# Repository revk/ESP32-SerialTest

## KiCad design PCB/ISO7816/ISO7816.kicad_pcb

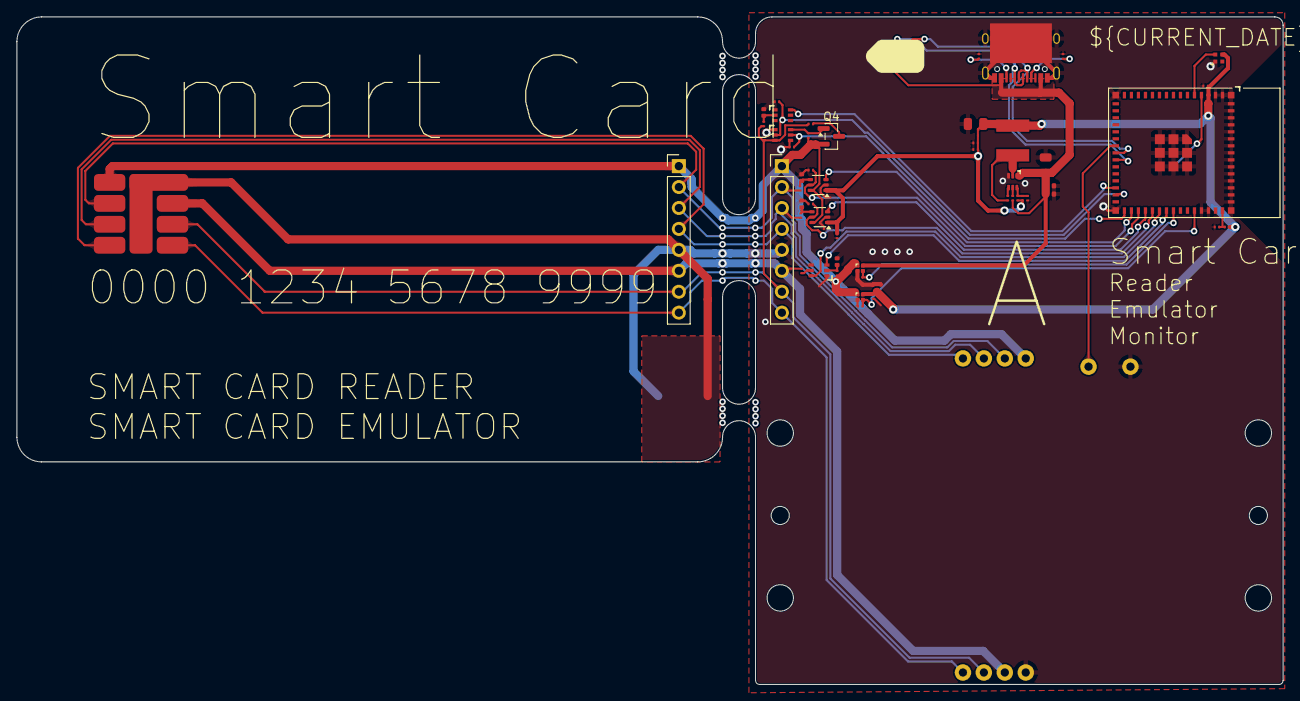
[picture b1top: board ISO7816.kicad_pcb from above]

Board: 2 copper layers, 153.6 x 81.0 mm, 54 parts (1 on the bottom side), 40 nets.

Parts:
C6: 1uF; C_0201
C15: 22uF 25V; C_0805
C16, C17: 100nF 25V; C_0402
C18, C21, C22, C23, C24, C25: 100nF; C_0201
C19: 18pF; C_0201
C20: 47uF 6V; C_0805
D1: XL-1010RGBC-WS2812B; SMD1010
D2, D3, D5, D6: DFN1006-2L
J1: Conn_01x02; AA-Pad
J2: ISO7816
J3, J4: Conn_01x08; PinHeader_1x08_P2.54mm_Vertical
J5: 7434L0825S01LF
J6: USB-C-Socket-H
J7: TC2030-USB-NL-DS; Tag-Connect_TC2030-IDC-NL_2x03_P1.27mm_Vertical
L2: 4.7uH; L_5x5
Q1, Q2, Q3: BSS138PS; SOT-363_SC-70-6
Q4: BSS84; SOT-23
R1: 20k; R_0201
R2, R3, R4, R12, R13, R17, R18, R19: 10k; R_0201
R5, R6, R8, R9, R20: 10R; R_0201
R10, R11: 5K1; R_0201
R14, R15: 150k 1%; R_0201
R16: 33k 1%; R_0201
U1: ESP32-S3-MINI-1-N4R2; ESP32-S3-MINI-1
U2, U6: SN74LVC1T45DCK; SOT-363_SC-70-6
U3: TPS562246; SOT-563
U4, U5: TPS22916CNYFPR; WCSP-4-0.78x0.78

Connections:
+3.3V: C19.2, C20.1, C21.2, C22.2, C23.2, C24.2, C25.2, D1.3 (-), L2.2, R2.1, R15.1, U1.3 (3V3), U2.1 (VCCA), U5.A2 (VIN), U6.1 (VCCA)
BST: C18.1, U3.4 (VBST)
C_3V3: R13.1, U1.41 (GPIO45), U5.B2 (ON)
C_4: J2.4 (C4), J3.4, J4.4, J5.4 (C4)
C_5V: R12.1, U1.38 (GPIO42), U4.B2 (ON)
C_8: J2.8 (C8), J3.8, J4.8, J5.8 (C8)
C_CLK: J2.3 (CLK), J3.3, J4.3, J5.3 (CLK), R8.2
C_CLK_E: R18.2, U1.35 (GPIO39), U6.5 (DIR)
C_CLK_IO: U1.34 (GPIO38), U6.3 (A)
C_INSERT: J5.9 (I1), U1.22 (GPIO18)
C_I/O: J2.7 (I/O), J3.7, J4.7, J5.7 (I/O), Q3.3 (SP), R1.2, R9.2
C_I/O_E: Q3.2 (GN), R4.2, U1.29 (GPIO34)
C_I/O_I: Q2.6 (DN), U1.28 (GPIO33)
C_I/O_O: Q3.5 (GP), R17.1, U1.31 (GPIO35)
C_RST: J2.2 (RST), J3.2, J4.2, J5.2 (RST), R20.2
C_RST_E: R19.2, U1.33 (GPIO37), U2.5 (DIR)
C_RST_IO: U1.32 (GPIO36), U2.3 (A)
C_VCC: J2.1 (VCC), J3.1, J4.1, J5.1 (VCC), Q4.2 (S), R3.2, R5.2, U2.6 (VCCB), U4.A1 (VOUT), U5.A1 (VOUT), U6.6 (VCCB)
C_VCC_I: Q1.6 (DN), U1.36 (GPIO40)
C_VPP: J2.6 (VPP), J3.6, J4.6, J5.6 (VPP), R6.2
C_VPP_I: Q1.3 (SP), U1.37 (GPIO41)
D+: J6.A6 (D+), J6.B6 (D+), J7.4 (D+), U1.24 (GPIO20)
D-: J6.A7 (D-), J6.B7 (D-), J7.2 (NC), J7.3 (D-), J7.6 (NC), U1.23 (GPIO19)
EN: R14.1, U3.5 (EN)
FB: C19.1, R15.2, R16.1, U3.6 (VFB)
GND: C6.2, C15.2, C16.2, C17.2, C20.2, C21.1, C22.1, C23.1, C24.1, C25.1, D1.2 (+), D2.1, D3.1, D5.1, D6.1, J1.1, J2.5 (GND), J3.5, J4.5, J5.5 (GND), J5.10 (I2), J6.A1 (GND), J6.A12 (GND), J6.B1 (GND), J6.B12 (GND), J6.S1 (SHIELD), J7.5 (GND), Q1.1 (SN), Q1.4 (DP), Q2.1 (SN), Q3.1 (SN), Q3.4 (DP), R4.1, R10.2, R11.1, R12.2, R13.2, R16.2, R17.2, R18.1, R19.1, U1.1 (GND), U1.2 (GND), U1.42 (GND), U1.43 (GND), U1.46 (GND), U1.47 (GND), U1.48 (GND), U1.49 (GND), U1.50 (GND), U1.51 (GND), U1.52 (GND), U1.53 (GND), U1.54 (GND), U1.55 (GND), U1.56 (GND), U1.57 (GND), U1.58 (GND), U1.59 (GND), U1.60 (GND), U1.61 (GND), U1.62 (GND), U1.63 (GND), U1.64 (GND), U1.65 (GND), U2.2 (GND), U3.3 (GND), U4.B1 (GND), U5.B1 (GND), U6.2 (GND)
LED: D1.4 (I), U1.5 (GPIO1)
unnamed: J1.2, U1.4 (GPIO0)
unnamed: J6.A5 (CC1), R10.1
unnamed: J6.B5 (CC2), R11.2
unnamed: D2.2, Q1.2 (GN), R5.1
unnamed: Q1.5 (GP), R6.1
unnamed: D6.2, Q2.2 (GN), R9.1
unnamed: Q3.6 (DN), Q4.1 (G), R3.1
unnamed: Q4.3 (D), R1.1
unnamed: C6.1, R2.2, U1.45 (EN)
unnamed: D3.2, R20.1, U2.4 (B)
unnamed: D5.2, R8.1, U6.4 (B)
SW: C18.2, L2.1, U3.2 (SW)
VBUS: C15.1, C16.1, C17.1, J6.A4 (VBUS), J6.A9 (VBUS), J6.B4 (VBUS), J6.B9 (VBUS), J7.1 (VBUS), R14.2, U3.1 (VIN), U4.A2 (VIN)

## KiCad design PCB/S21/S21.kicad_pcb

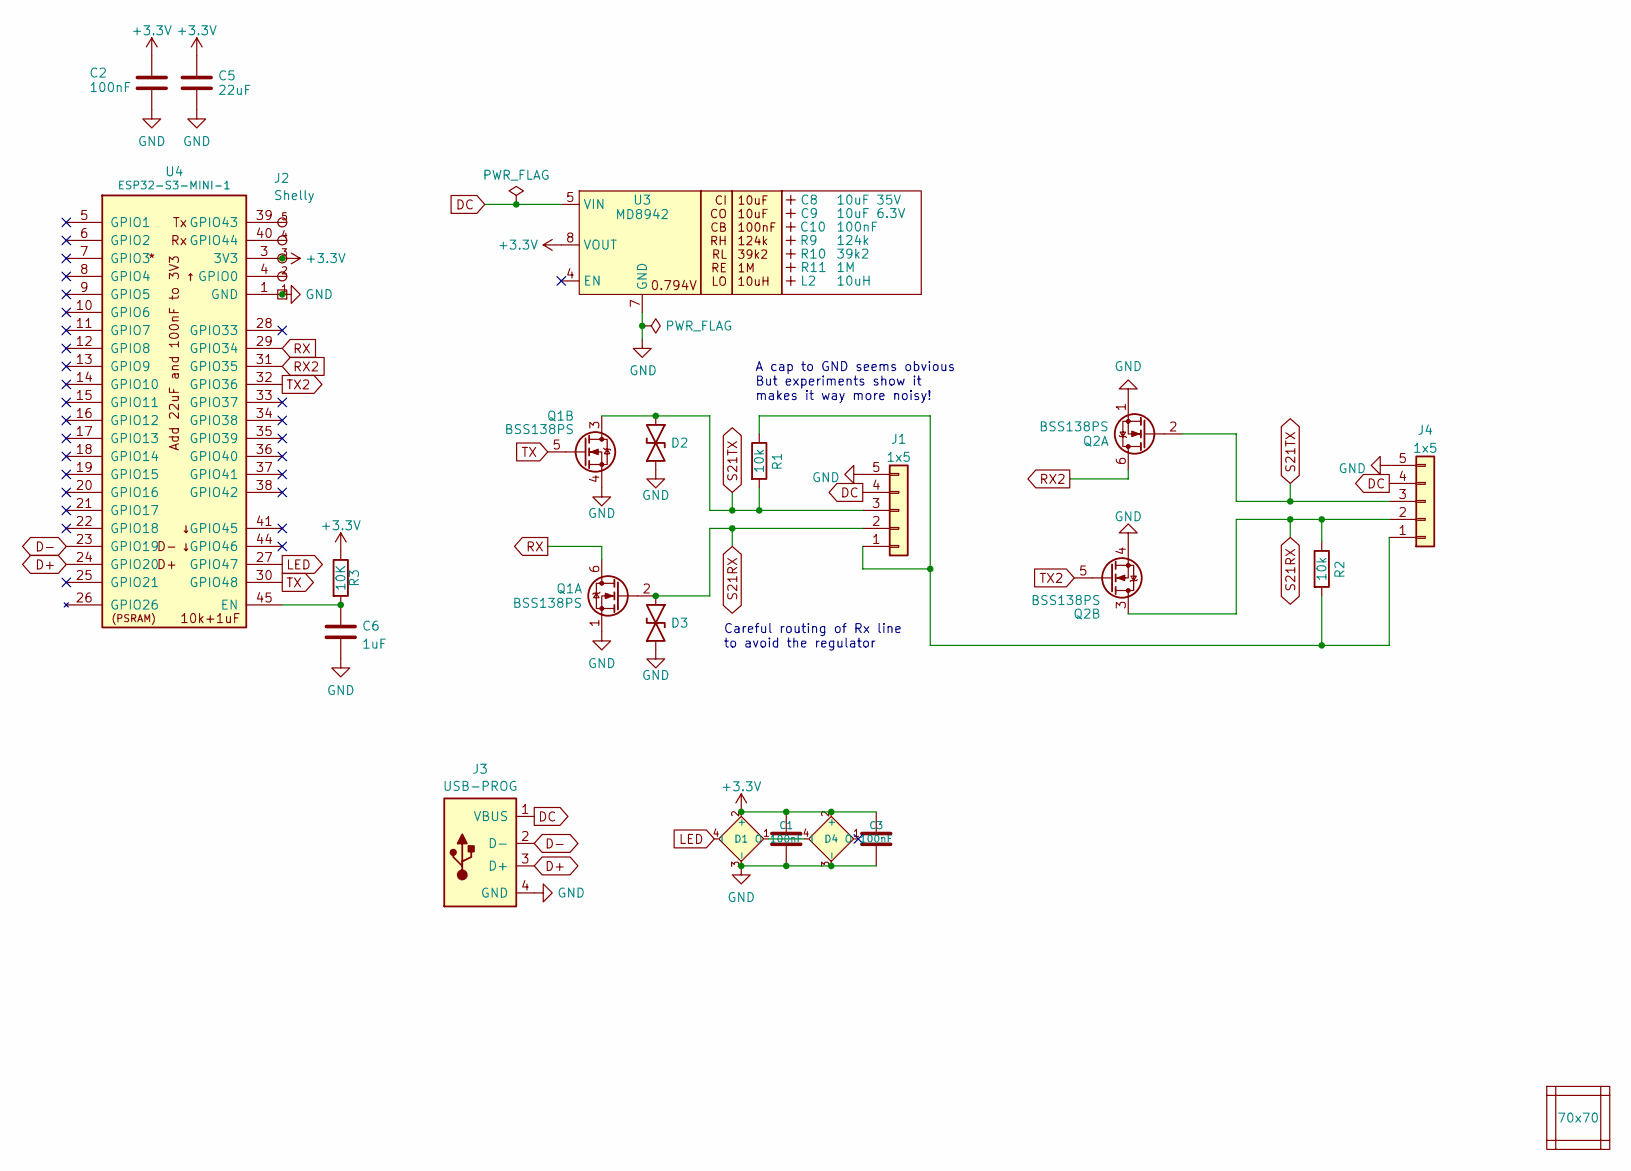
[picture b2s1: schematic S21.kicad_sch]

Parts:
C1, C2, C3: 100nF; C_0402
C5: 22uF; C_0603
C6: 1uF; C_0402
C8: 10uF 35V; C_0603_; LCSC Part # C194427
C9: 10uF 6.3V; C_0603_; LCSC Part # C1691
C10: 100nF; C_0603_
D1, D4: XL-1010RGBC-WS2812B; SMD1010; LCSC Part # C5349953
D2, D3: DFN1006-2L; LCSC Part # C5137770
J1, J4: 1x5; JST_EH_S5B-EH_1x05_P2.50mm_Horizontal; LCSC Part # C265103
J2: Shelly
J3: USB-PROG
L2: 10uH; L_4x4_
PCB1: 70x70; PCB7070
Q1, Q2: BSS138PS; SOT-363_SC-70-6; LCSC Part # C193381
R1, R2: 10k; R_0402
R3: 10K; R_0402
R9: 124k; R_0402_
R10: 39k2; R_0402_
R11: 1M; R_0402_
U3: MD8942; SOT-23-6-MD8942; LCSC Part # C2684786
U4: ESP32-S3-MINI-1; LCSC Part # C3013941
V1, V2, V5, V6: VCUT70N

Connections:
+3.3V: C1.1, C2.1, C3.1, C5.1, D1.2 (+), D4.2 (+), J2.3 (3V3), R3.1, U3.8 (VOUT), U4.3 (3V3)
D+: J3.3 (D+), U4.24 (GPIO20)
D-: J3.2 (D-), U4.23 (GPIO19)
DC: J1.4, J3.1 (VBUS), J4.4, U3.5 (VIN)
GND: C1.2, C2.2, C3.2, C5.2, C6.2, D1.3 (-), D2.1, D3.1, D4.3 (-), J1.5, J2.1 (GND), J3.4 (GND), J4.5, Q1.1 (SN), Q1.4 (DP), Q2.1 (SN), Q2.4 (DP), U3.2 (GND), U3.7 (GND), U4.1 (GND), U4.2 (GND), U4.42 (GND), U4.43 (GND), U4.46 (GND), U4.47 (GND), U4.48 (GND), U4.49 (GND), U4.50 (GND), U4.51 (GND), U4.52 (GND), U4.53 (GND), U4.54 (GND), U4.55 (GND), U4.56 (GND), U4.57 (GND), U4.58 (GND), U4.59 (GND), U4.60 (GND), U4.61 (GND), U4.62 (GND), U4.63 (GND), U4.64 (GND), U4.65 (GND)
LED: D1.4 (I), U4.27 (GPIO47)
unnamed: D1.1 (O), D4.4 (I)
unnamed: J1.1, J4.1, R1.1, R2.2
unnamed: J2.2 (0), U4.4 (GPIO0)
unnamed: J2.4 (Rx), U4.40 (GPIO44)
unnamed: J2.5 (Tx), U4.39 (GPIO43)
unnamed: C6.1, R3.2, U4.45 (EN)
RX: Q1.6 (DN), U4.29 (GPIO34)
RX2: Q2.6 (DN), U4.31 (GPIO35)
S21RX: D3.2, J1.2, J4.2, Q1.2 (GN), Q2.3 (SP), R2.1
S21TX: D2.2, J1.3, J4.3, Q1.3 (SP), Q2.2 (GN), R1.2
TX: Q1.5 (GP), U4.30 (GPIO48)
TX2: Q2.5 (GP), U4.32 (GPIO36)

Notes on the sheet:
Careful routing of Rx line to avoid the regulator
A cap to GND seems obvious But experiments show it makes it way more noisy!

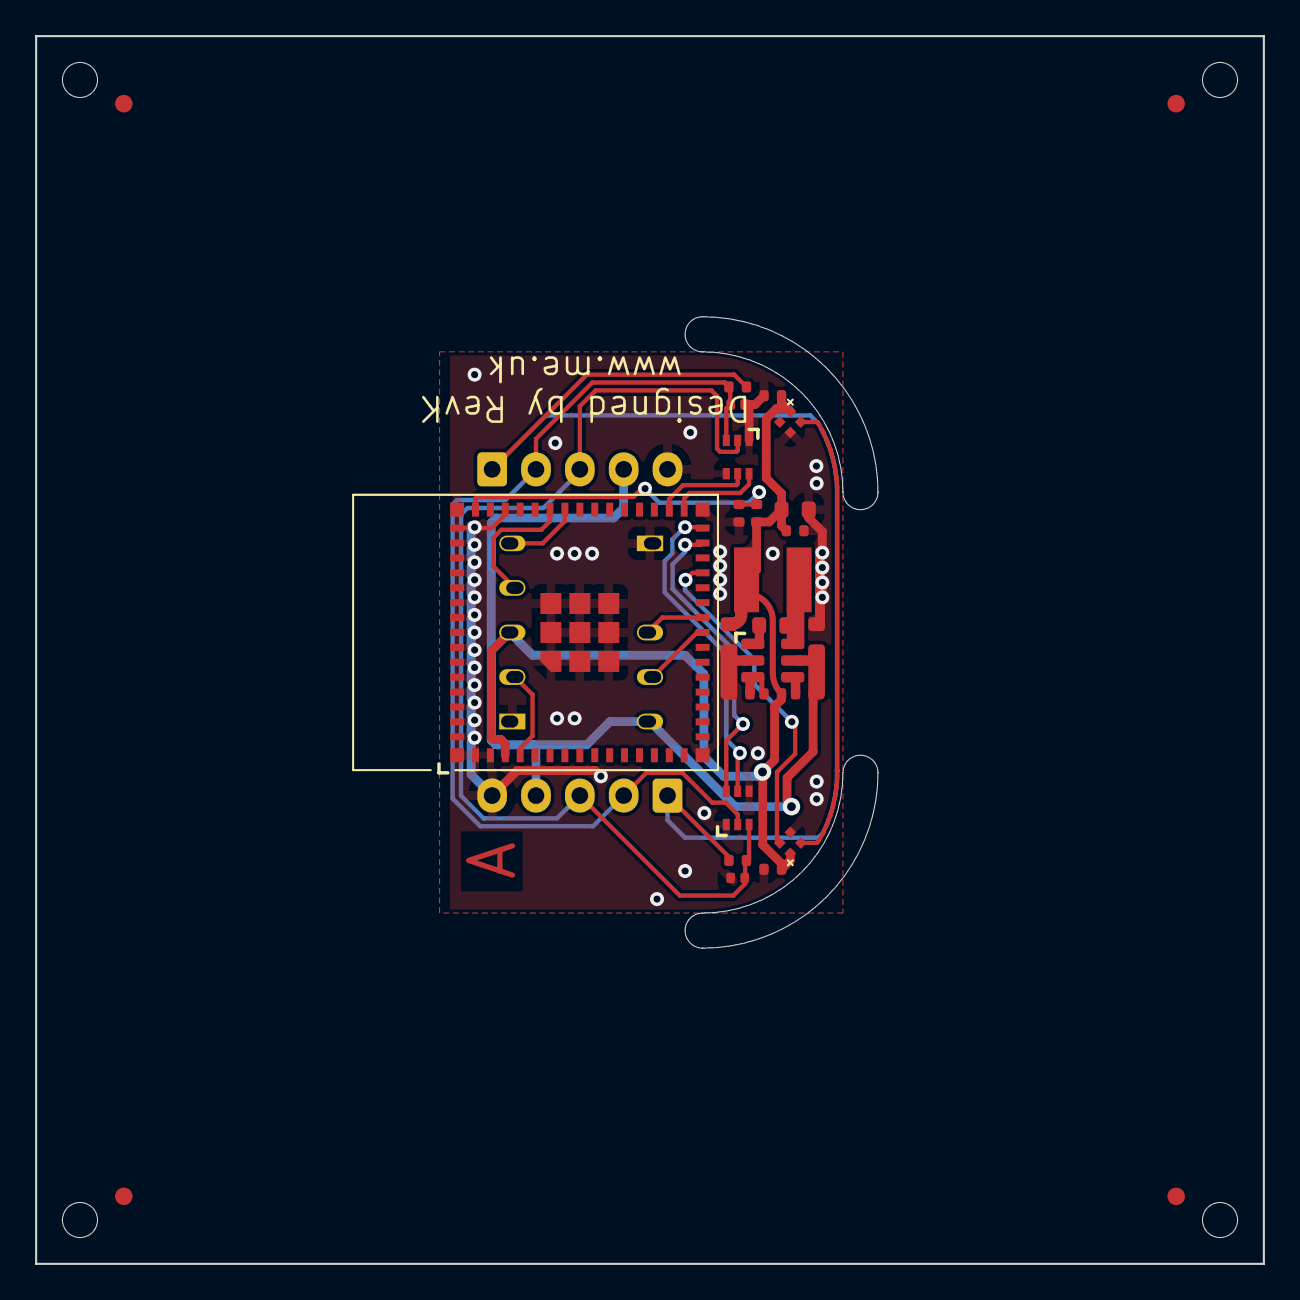
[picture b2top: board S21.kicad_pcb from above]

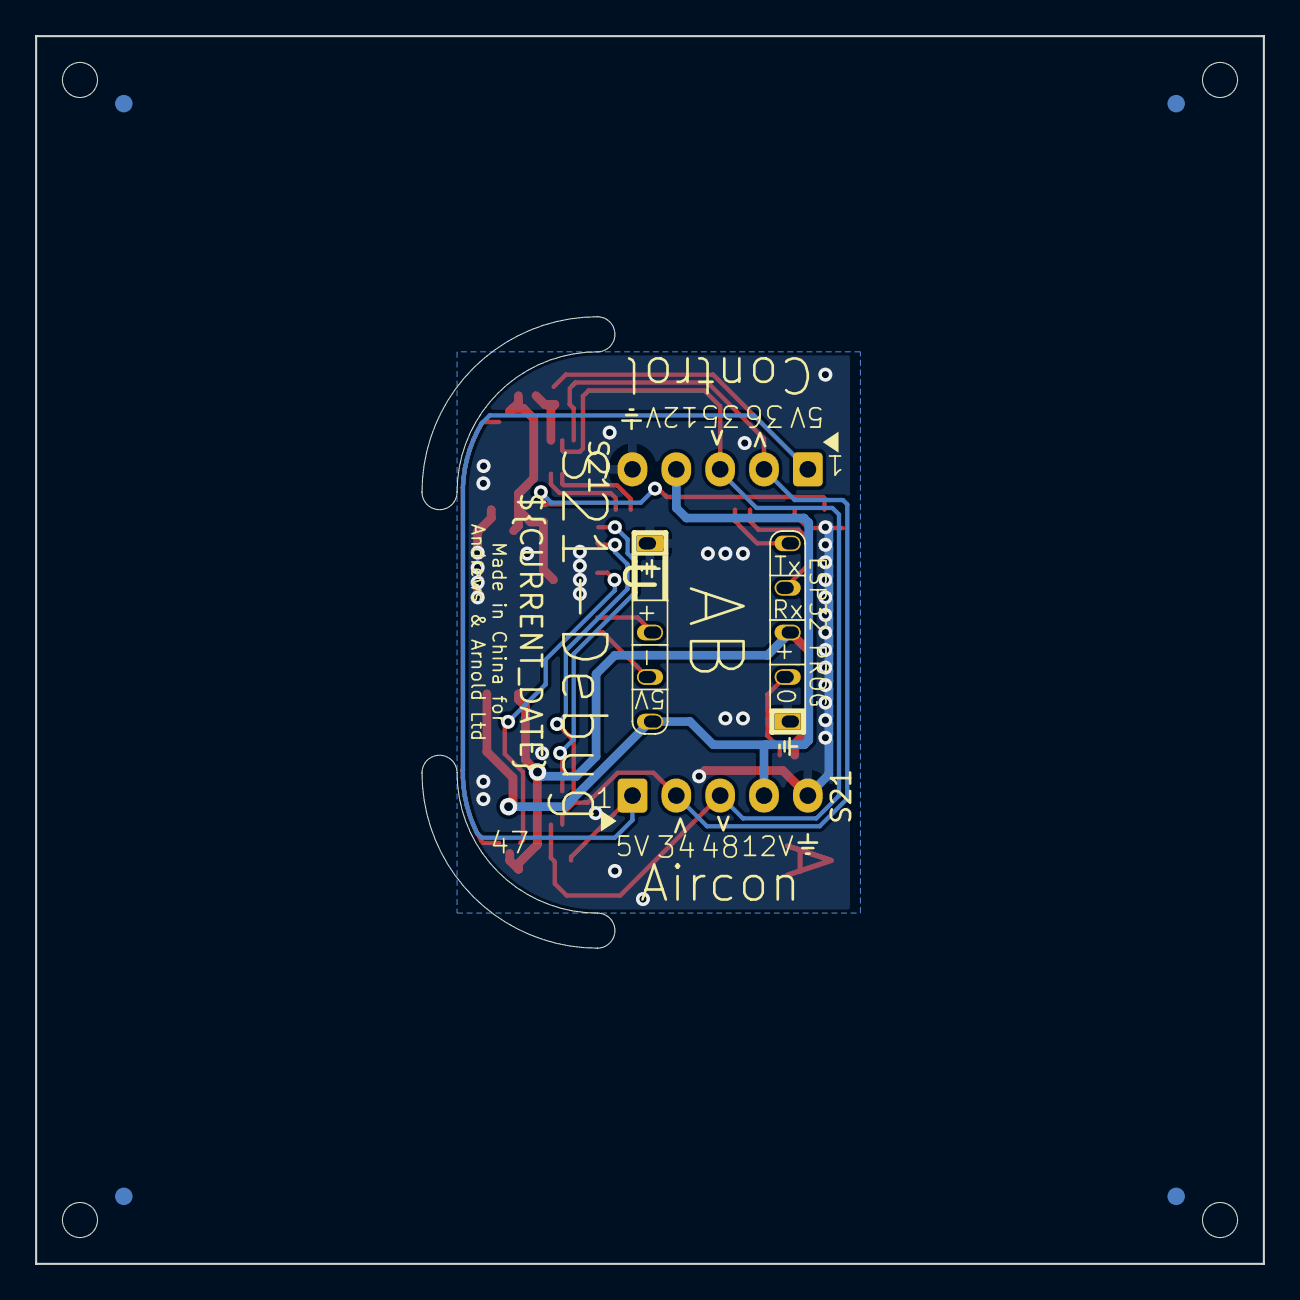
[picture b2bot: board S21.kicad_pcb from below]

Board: 2 copper layers, 70.0 x 70.0 mm, 32 parts (3 on the bottom side), 18 nets.

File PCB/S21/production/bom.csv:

Designator,Footprint,Quantity,Value,LCSC Part #
"C1, C2, C3",C_0402,3,100nF,
C10,C_0603_,1,100nF,
C5,C_0603,1,22uF,
C6,C_0402,1,1uF,
C8,C_0603_,1,10uF 35V,C194427
C9,C_0603_,1,10uF 6.3V,C1691
"D1, D4",SMD1010,2,XL-1010RGBC-WS2812B,C5349953
"D2, D3",DFN1006-2L,2,~,C5137770
"J1, J4",JST_EH_S5B-EH_1x05_P2.50mm_Horizontal,2,1x5,C265103
L2,L_4x4_,1,10uH,
"Q1, Q2",SOT-363_SC-70-6,2,BSS138PS,C193381
"R1, R2, R3",R_0402,3,10k,
R10,R_0402_,1,39k2,
R11,R_0402_,1,1M,
R9,R_0402_,1,124k,
U3,SOT-23-6-MD8942,1,MD8942,C2684786
U4,ESP32-S3-MINI-1,1,ESP32-S3-MINI-1-N4R2,C3013941

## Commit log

2025-11-13 Started
2025-11-13 Release
2025-11-13 Render and cases
2025-11-13 Fixed render
2025-11-16 Started ISO7816 module
2025-11-16 Tweak PCB
